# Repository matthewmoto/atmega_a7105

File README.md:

# ATMega A7105 Mesh Network Library #

# What Is This? #
The ATMega A7105 project is a radio library and mesh network stack built for the 
Arduino environment (currently only tested on ATMega328p). The radio library and
mesh library are split so you can use the radios without the mesh logic if you like.

The primary goal for this project is to allow a simple lightweight self-healing network
of microcontrollers to be able to share data easily and overcome the limitations of 
the platform (namely very little RAM and short radio range). For more details on the 
mesh topology and design, see the [Mesh Layout Section](#Mesh-Layout) below.

# Background #

In early 2015, I  bought a handful of what I thought were NRF24L01 radio breakouts
in order to make [my 2015 Halloween Decorations](https://youtu.be/kfExGzUOxbg) wireless. 
Having run 150' of security wire the previous year, accidentally cut a critical line 
partway into the set-up and collecting it all back up the next day, I had a pretty strong motivation to 
make the switch.

In my haste to buy radios, I didn't analyze the Engrish on the product page (I was buying through
DX) and ended up with a bunch of A7105 breakouts (Also known as XL7105-SY-B).

There wasn't a bunch of useful code out there for these chips (the rcgroups.com guys
were probably the most mature but they were only really using a simple protocol for 
controlling mini quadcopters).

Lamenting my poor selection and thinking to just buy the correct radios, I looked 
into the NRF24L01's further and found I didn't really dig what was available for those either (the RF24Mesh
project, cool as it is, required a master node running for all the routing to work).

As a final bad decision (I am not a smart man...), I figured I could make a general purpose lightweight mesh stack that
would solve my problems and put the 10-odd radios that I had purchased to good use.

This code is the result of those bad decisions. After having implemented the mesh, I realize
the radio hardware itself isn't that important as far as the Mesh logic goes 
(it can be adapted to the NRF24L01's or similar at some point). However, I'm using A7105's 
for now. The good news is you can get a pair of radios for under $5USD.

# Hardware #
Because the A7105 is a 3.3V chip and the Pro Mini's I use are 5V, I decided to build shields that had
logic level convertors and a voltage regulator on board so I could just plug the boards in and make them
play nicely together. Additionally, I'm using one of the GIO pins of the radio as a "WTR" pin (it basically
goes low when the radio is done transmitting or receiving so we can use an interrupt to figure out when 
data is ready to read or is done being sent over the air) and the other as the MISO line for the SPI bus. 
Unfortunately, the GIO pins on the radio aren't nice enough to go high-Z when the chip select line is high so 
I also included a tri-state buffer to do that in case this node is used on a bus with other SPI devices.
Finally, the A7105 uses a weird 2MM pitch metric header to mount so the shield also accommodates that.

If you're using 3.3V Arduino's, you won't really need any of this (except possibly the MISO tri-state buffer
if you plan on talking to other SPI devices), but I like 5V stuff since all my other hardware (relay boards, 
MOSFETS, etc) for my Halloween project are 5V.

The Eagle files for my shield are included in the code repository in the hardware/ directory and the PCB can
be ordered on [OSH Park](https://oshpark.com/shared_projects/frDcWgtm) This is not a plug, it's just 
where I had my fabricated. I included the original design files and 
Bill of Materials in case you want to make them yourself or use a different fab house. I can post the Gerber 
files if anyone wants those instead.

This is the rendering of the shield:

Here is what the assembled radio node looks like:

And here is what it looks like with the Pro Mini and XL7105 removed:

# Getting Started #

A single node mesh isn't very interesting. Thusly, to start doing things other than being a 
lonely radio singing to yourself, you'll need a pair of nodes to make a mesh.

I included a few simple example sketches to use when you're getting started with the
code. These include test programs used to develop the mesh code and actual production 
code used in the first project (my Halloween 2015 house decorations).

## Register Host Test ##
This sketch can be found at examples/register\_host\_test/atmega\_a7105.ino.  To build it, simply copy 
it to the root of the repo, and do the usual scons build/upload.

The Register Host Test example is meant to be used with the A7105 Shield, but see the hook-up instructions
in the top of the sketch if you want to rig up your own harness.  This harness is mean to be connected and 
then poked with either the Serial Mesh Interface (see below) or a sketch of your own making.

## Serial Mesh Interface ##
This is the firmware for the A7105 Serial Mesh Interface. This firmware                
runs on a Pro Mini (or other Arduino) connected to a host machine via in FTDI
serial interface.

The Serial interface runs at 115200 baud and the serial\_mon.sh script can be used
with an argument (e.g. /dev/ttyUSB0) to start communicating with the node. This is the 
most useful example and is the actual bridge firmware used for my Halloween 2015 Prop Controller
script (there is a Python library that sits on the serial port and talks to the mesh).

See the Hook-Up instructions in the comments of the sketch for help getting this connected if you aren't
using the Pro Mini shield.
                                                                                       
NOTE: All Serial commands return either the specified "Response:" response defined below or 
the universal error response that looks like this: `"ERROR,ERROR_ID,MSG\r\n"`

Where `ERROR_ID` is a non-zero integer defined below and `MSG` is a contextually helpful
plaintext ascii string to aid in identifying the issue.

All responses or interrupting data will be one or more comma delimited lines ending in `/r/n`.

Serial Commands:                                                                       
```  
  ECHO: Turns on command echoing                                                       
  Response: ECHO,<TOGGLED>
  NOTE: TOGGLED is 1/0 for on/off (respectively) (default is OFF)                      

  LISTEN: Listen for broadcast events from the mesh.
    Response: N lines of REGISTER_VALUE,REGISTER_NAME,REGISTER_VALUE\r\n
    Possible errors: A7105_Mesh_NOT_ON_MESH
    Note: No other commands may be performed during a LISTEN. To exit LISTEN,          
          pass a byte (or less than 120 bytes) and wait for the string                 
          "READY\r\n" to come back, before issuing any commands.                       
          When entering LISTEN mode, the Arduino will first send back                  
          the line "LISTEN\r\n" as an ACK that it is now listening.                    

    Possible errors: A7105_Mesh_MESH_ALREADY_JOINING
                                                                                       
  RESET:    Leave the current mesh (no longer participate), reinitialize               
            the A7105 radio and generate a new unique ID.                              
    Response: INIT,<SUCCESS>,UNIQUE_ID              
    Possible errors: A7105_Mesh_NOT_ON_MESH
    NOTE: SUCCESS is 0 or 1 for failure/success respectively and                       
          UNIQUE_ID is an ASCII_HEX string for the 2-byte unique ID                    
          generated for this instance.                                                 

  PING: Ping the mesh to get the connected nodes
    Response: PING,NODE_ID_1,NODE_ID_2,.....NODE_ID_N (where node ID's are integers of found nodes on the mesh)
    Possible errors: A7105_Mesh_NOT_ON_MESH, A7105_Mesh_BUSY

  LIST_REGISTERS: Get all register names on the mesh
    Response: LIST_REGISTERS,REGISTER_NAME_1,REGISTER_NAME_2,....,ERRORS
    Possible errors: A7105_Mesh_NOT_ON_MESH, A7105_Mesh_BUSY
    
    NOTE: The ERRORS field in the response is a numeric value (0-255)
          denoting the number of nodes that returned incomplete data
          (either the number of registers or names of registers served)
          so if this value is non-zero, the results should be considered
          incomplete

  GET_REGISTER,<REGISTER_NAME>,<FORMAT>: Get's the value of a single register identified by <REGISTER_NAME>
    Response: GET_REGISTER,REGISTER_NAME,REGISTER_VALUE
    POSSIBLE errors: A7105_Mesh_NOT_ON_MESH, A7105_Mesh_INVALID_REGISTER_INDEX
  
    NOTE: FORMAT can be "STRING" for ASCII data, "BINARY" for binary (output will be
          ASCII hex), or "UINT32" for unsigned integer data.

  SET_REGISTER,<REGISTER_NAME>,<FORMAT>,<REGISTER_VALUE>: Set's the value of a single register identified by <REGISTER_NAME>
    Response: SET_REGISTER_ACK,REGISTER_NAME
    POSSIBLE errors: A7105_Mesh_NOT_ON_MESH, A7105_Mesh_INVALID_REGISTER_INDEX, A7105_Mesh_INVALID_REGISTER_VALUE
    
    NOTE: REGISTER_VALUE is interpreted differently depending on FORMAT. If FORMAT is:
      * STRING: REGISTER_VALUE is sent as a string whose value is terminated by /r/n on
                the serial terminal (not included in value sent).
      * BINARY: REGISTER_VALUE is taken to be a byte-aligned ASCII_HEX string whose value is sent
                as a raw binary value.
      * UINT32: REGISTER_VALUE must be an ascii string representing a numerical value between
                0 and UINT32_MAX.

  VALUE_BROADCAST,<REGISTER_NAME>,<FORMAT>,<REGISTER_VALUE>: Broadcasts a value for a register (does not need to actually
                                                             be hosted).
    Response: READY 
    Possible errors: TBD
      
    NOTE: See SET_REGISTER above for possible values of FORMAT.
 
LISTEN-Mode Data (not directly associated with a command):
  REGISTER_VALUE,<REGISTER_NAME>,<REGISTER_VALUE>
  If a node pushes a REGISTER_VALUE packet out without a node-id, it is considered a value broadcast 
  and will be pushed to the serial terminal at the time of arrival, however it will not precede the 
  current operation. 
```
## Building The Code ##
The example sketches are all based on building with [arscons](https://github.com/suapapa/arscons).

However, there are a few caveats. Namely, the code expects an Arduino distribution in the resources/
directory. One is included, but needs to be unpacked first:
` cd resources/ ; unzip arduino-1.6.1-linux32.tar.xz`

Also, arscons expects the sketch name to be the same as the directory it is in (the reason while all examples
are named atmega-a7105.ino in their respective directories).

To build an example (e.g. the serial_mesh_interface example) and push it to an arduino:
```
  (from the repo root)
  $ cp examples/serial_mesh_interface/atmega_a7105.ino .
  scons ARDUINO_PORT=/dev/ttyUSB0 upload #substitute your serial port name where applicable
```

To build the current sketch (atmega_a7105.ino), type:
`scons`

To clean:
`scons -c`

To upload to your board:
`scons ARDUINO_PORT=YOUR_SERIAL_PORT upload`

Note: check out the arscons page and update your arscons.json configuration file if
you aren't running a 5V 16Mhz Pro Mini via a FTDI programmer as I am.

Also, if you are using the graphical Arduino IDE, feel free to just copy the libraries from their directories
and place in your Arduino library path. I haven't tested this method yet so it may need a little fiddling 
to get it working.

# Debugging Your Nodes #

Sometimes the mesh won't do what you want. This might be a bug, it might be your code or (most likely) it might 
be a connector that has a bit of solder on it or is bent or something else that makes me FURIOUS, AAAAAHHHHH!!!

Regardless, the best way to see what your radio is doing is to toggle the  just uncomment the line:
`#define A7105_MESH_DEBUG` in a7105_mesh.h. This will output internal state and received packet dumps to help diagnose problems.

There is also a script (one liner) in the repository called "serial_mon.sh", running it fires 
up screen and archives the output to screenlog.0
` ./serial\_mon.sh /dev/ttyUSB0`  

# Mesh Layout #

## Simplified Explanation ##
In order to ease into what is meant in this project by the word "Mesh," presented here is a 
simplified idea of how things go.

Given N nodes (nodes being ATMega microcontrollers with a radio attached), they all talk to 
each other and serve registers (values with names attached).  For a concrete example, consider
3 nodes: A, B and C.  A serves a register "Motion" that correlates to a motion sensor attached to
it. B doesn't serve any nodes, but responds to certain broadcasts (e.g. "BLOW\_FOG") and C doesn't
serve registers either, but runs a serial interface to a host computer for a program or user to poke 
the mesh.

In this example, for there to be a "Mesh," the nodes need to agree on a few things:
 1. They are on a mesh
 2. What their "node ID" is (a value from 1-255 to identify the node on the mesh).
 3. That they have a 16-bit unique ID

To do this, each node starts broadcasting (at a pseudo random interval), that it wants to join a mesh 
and that it's node ID is 1 (everybody starts at 1), and it's unique ID is whatever it is. As these packets
go out over the radio, any conflicts (duplicated node ID's ) are seen by the nodes and CONFLICT_NAME packets
are sent out as a response.  The node with the lower unique ID increments their requested node ID and starts 
the JOIN process over again. 

If a node get's through the multi-second JOIN broadcasts without having CONFLICTS come back for their selected node ID, it assumes itself 
to be "on the mesh with that ID" It's important to note, that the conflict packets can come at any time and the rules still
apply (the lower unique ID always re-joins as a different ID). It is this property that makes the mesh "self 
healing" where if two groups of nodes exist that can't talk to each other (two separate meshes) suddenly can
communicate (e.g. by moving closer together), they will conflict and re-order themselves to be a single mesh.

So, back to the example, a bunch of JOIN packets fly around. A few CONFLICT's happen and the nodes A, B and C
join as 1,2 and 3 (not necessarily in that order). Now, if node C starts sending requests to get the value of
the "Motion" register, it doesn't care what node actually hosts that value, just that one does and value 
responses come back (i.e. a nodes ID isn't considered a permanent thing).

All nodes respond to PING packets with PONG packets (for simple presence detection). The PING-ing node keeps a 
presence bitmask (255 bit) that can be used to iterate and poke every seen node on the mesh.  For discovering what
registers are available on a mesh, a node performs the following steps:
 1. PING all the nodes to find available nodes
 2. For every found node, query how many registers it serves (GET_NUM_REGISTERS packet)
 3. For the current node, iterate from 0 to N-1 (N being the number of served registers) and query the register name for each (GET_REGISTER_NAME)

If a node knows the name of the register it wants to query, it can simply send a GET_REGISTER packet with the name of the register in question
and expect a REGISTER_VALUE packet in response (assuming the node serving that register is currently available). If a node wants to remotely set a
register value, it can likewise send a SET_REGISTER packet with the name and new value of the register. For SET_REGISTER requests, a 
SET_REGISTER_ACK packet is expected to come back with either success or some error message from the remote node explaining an error (in ascii).

Beyond this, there is only one special case for getting/setting registers: value broadcasts. Since node numbering starts at 0, if a 
REGISTER_VALUE packet is seen with a node ID of 0 in the header, it is assumed to be a broadcast. These broadcasts are repeated through the
mesh by all nodes and are meant for notification of global events. They are not ACK'd by any nodes. Broadcasts can be useful if a node needs to
push a notification to the mesh rather than being polled for a value.

## Primary Canons ##
 1. As stateless as practical. Large state means high RAM usage and inflexible rules. Both are catastrophic.
 2. Requesters are responsible for retries and request state management.
 2. Global registers. Nodes serve registers, it doesn't matter who or where (at the API level).
 3. All non-broadcast packets must be ACK'd (either explicitly or with a response packet)
 4. Max of 255 nodes (0 is a special value meaning broadcast)
 5. Joining is the responsibility of good citizen nodes. There is no gatekeeper.
 6. Easy of use and reliability are the targets, security is not very important (it's a low power mesh network)
 7. Avoid traffic contention whenever possible (don't repeat packets blindly).

## Packet Characteristics ##

All packets should have the following characteristics:

```OPERATION | SEQ-NUM/HOP-COUNT | NODE_ID | UNIQUE_ID | <operation-specific-data>```

Packets are 64 bytes long at a maximum, operation specific data
is a maximum of 60 bytes long.

The packet header looks like this:
  1. Byte 0: The operation (PING, JOIN, etc)
  2. Byte 1: The sequence number and hop count (upper nibble is sequence, lower is hop)
             See notes below on these fields.
  3. Byte 2: The node-ID of the sender (1-255, 0 is reserved)  
  4. Byte 3-4: The unique-ID of the sender (1-16535, 0 is reserved)

### Hop Count ###
The hop count in the SEQ-NUM/HOP-COUNT byte is a number 0-15(max) denoting
how many times a packet has been repeated by somebody other than the sender.

When a node sends a packet normally, the hop count should be 0. Every node that
repeats the packet should do so verbatim except incrementing the hop count nibble 
by one so the next node will know whether or not the packet can be repeated again.

### Sequence Number ###
The sequence number nibble in the SEQ-NUM/HOP-COUNT byte is a number (0-15) that
is maintained by each node when sending requests (or value broadcasts). This number 
is incremented (15 + 1 rolls over to 0) after each sent packet. Thusly, two identical
requests sent back-to-back from a node can be distinguished from the same packet being
repeated by other nodes in the mesh (since we don't know the route a packet will take,
hop count cannot be used for this reliably).

## Maintaining Node Numbering ##

  To be as effective as possible at correctly assigning and maintaining
  the node numbering on the mesh as nodes come and go, each node generates
  a unique ID (16 or 32 bit, not sure yet) to be included in the packets
  they send.  This deals with the problem of joining the mesh as a certain
  node number that's already in use (the node using it will respond with a 
  CONFLICT_NAME packet) like this:
    `CONFLICT_NAME | HOP/SEQ | NODE_ID | UNIQUE_ID`

  Also, this deals with the issue of nodes that appear thinking they're
  already part of the mesh (if they were blocked or something while somebody
  joined and took their ID).

  For example, if we have 5 nodes (1-5) on the network and node 2 is blocked from 
  the mesh signals (we'll call this node ABC) for a few seconds while 
  a 6'th node (DEF) joins (taking the node 2 name).

  If a request comes from node 1 to get the listing of register names 
  from node 2 (which is actually 2 nodes thinking they're on the mesh
  right now since nobody has pinged while they're both on), they both
  will respond.

  How do we deal with ABC and DEF both thinking they're node 2? They
  can't figure it out before-hand because there isn't any traffic going
  on.  They will see each others' REGISTER_NUM response.

  The requester will process whichever REGISTER_NUM response comes first
  but the nodes themselves will likely see each other's response and 
  the one with the lower unique ID will have to re-join.

  The requester, will then likely send GET_REGISTER_NAME requests
  to the first-responding node while the other rejoins. Since there
  is only one node 2 now, everything will proceed as usual. 

  Additionally, the requester will save the unique ID of the node that
  responded to REGISTER_NUM to use for filtering GET_REGISTER_NAME 
  responses as well.

## Joining ##
  To join, a node must broadcast a "JOIN" packet at a sub-second frequency
  for multiple seconds before it can declare itself "JOINED." 
  
  The JOIN packet looks like this:
    `JOIN | HOP/SEQ | NODE_ID | UNIQUE_ID |`

  During the time it broadcasts, it must honor "CONFLICT" packets from other
  nodes. These should only come from nodes with the same NODE_ID being 
  requested but having a different UNIQUE_ID to indicate that NODE_ID is
  already taken.

  If the joining node receives a CONFLICT, it can only join by restarting
  the process with a different NODE_ID.

## Ping ##
  Detects presence prior to global operation, has timeout after which
  the Presence Table is considered accurate for the next operation.

  The PING packet looks like this:
    `PING | HOP/SEQ | NODE_ID | UNIQUE_ID`

  All nodes on the network respond (after a node-id delay) with:
    `PONG | HOP/SEQ | NODE_ID | UNIQUE_ID`

## Get Register Names (directed, retry) ##

Getting register names is available to make the mesh discoverable
with interactive terminals or more powerful hardware. The process
of getting all registers on the network is:
 1. Ping the mesh to get presence info
 2. Iterate each found node and send a GET_REGISTERS packet
 3. The node responds with the number of registers
 4. Iterate the number of registers and GET_REGISTER_NAME for each
 5. The node responds with the name of each register 

  The GET_NUM_REGISTERS packet looks like this:
    `GET_NUM_REGISTERS | HOP/SEQ | NODE_ID | UNIQUE_ID | TARGET_NODE_NUM`
  
  The NUM_REGISTERS packet response looks like this:
    `NUM_REGISTERS | HOP/SEQ | NODE_ID | UNIQUE_ID | NUM_REGISTERS`

  The GET_REGISTER_NAME packet looks like this:
    `GET_REGISTER_NAME | HOP/SEQ | NODE_ID | UNIQUE_ID | TARGET_NODE_NUM | REGISTER_INDEX`

  The response REGISTER_NAME packet looks like this:
    `REGISTER_NAME | HOP/SEQ | NODE_ID | UNIQUE_ID | REGISTER_NAME_LEN |REGISTER_NAME | REGISTER_INDEX`

  Note: If the register index is invalid, the response should just 
        have a REGISTER_NAME_LEN of 0

## Get Register ##

  The process of getting a register value is accomplished by 
  the requester sending out a broadcast packet to request
  the value of a register. The owner of that register then responds
  with a directed packet to the original requester.

  The GET_REGISTER packet looks like this:
    `GET_REGISTER | HOP/SEQ | NODE_ID | UNIQUE_ID | REGISTER_NAME_LEN | REGISTER_NAME`
   
  The responder (if there is one), sends back a REGISTER_VALUE packet like this:
    `REGISTER_VALUE | HOP/SEQ | NODE_ID | UNIQUE_ID | REGISTER_NAME_LEN | REGISTER_NAME | REGISTER_VALUE_LEN | REGISTER_VALUE`

NOTE: If NODE_ID = 0, the REGISTER_VALUE packet is considered to be a broadcast. Unique_ID must still be specified

## Set Register ##

  Setting a register is similar to getting a register value, except
  it's all in one packet so there are limits on the size of the register name/value.
  
  The SET_REGISTER packet looks like this:
    `SET_REGISTER | HOP/SEQ | NODE_ID | UNIQUE_ID |REGISTER_NAME_LEN | REGISTER_NAME | REGISTER_VALUE_LEN |REGISTER_VALUE`

  If there is a node servicing that register (and the register can be set), it responds like this:
    `SET_REGISTER_ACK | HOP/SEQ | NODE_ID | UNIQUE_ID | TARGET_NODE_NUM | ERR_MSG_DATA | NULL_BYTE`

NOTE: If there is an error setting a register and the managing node
wants it known (always a good idea), they should include an ascii 
error message at the tail (null terminated) explaining what happened
so the developer can easily diagnose issues.
If there is ERR_MSG_DATA before the NULL_BYTE, the register was set successfully.

## Node Characteristics ##

### Salt ###

  Each node has a unique ID (salt) used to handle identify conflicts.
  Nodes on a mesh are numbered 1-255, but this is handled dynamically
  so the salt is used to identify conflicts joining and for nodes
  responding to the same request if they didn't figure out the 
  conflict before it came.

### Presence Table ###

  A 255-bit bitmask (32-byte) is used to keep track of the node-id's
  seen recently for certain operations. It is refreshed only for these
  operations (like getting all registers on the mesh).

### Short Packet History ###
 
  A few (2-3 likely) packets are kept in memory to use for rebroadcasting
  packets as well as avoiding bouncing packets we already re-broadcast.
    
  This is done with a circular buffer at the moment. 

### Target Node Cache ###
  Each node saves the node-id and/or unique-id of a node it is corresponding with
  directly. These values are used to filter response packets a requesting node
  is interested in.

### Handled Request Cache ###
  This is a cache that stores metadata about recently handled requests (operation,
  sequence number, unique ID of requester) used to prevent responding to a request
  more than once as it bounces around the mesh.

### Packet Filtering ###
  Nodes filter packets for requests, responses and repeating. Below are details on the
  algorithm for each.

#### Requests ####
Requests are filtered using the "Handled Request Cache" detailed above. If a
node sees the same request it just handled, it will ignore that request.  Another
identical request from the same requesting node *will* be handled due to the fact that
the new request will almost be guaranteed to have a different sequence number than the one in the cache.    

#### Responses ####
Response packets are filtered out by utilizing the "Target Node Cache" described above.
If either a node-id and/or a unique-id are specified in the cache, only packets from those
id's will be processed by us as responses. This helps us to manage requests in the state machine such
as GET_NUM_REGISTERS where we will then know which NUM_REGISTERS packet to pay attention to
if it comes back (since it will be from the node we originally specified).

Also, this prevents us from having our target node ID swapped in the middle of long-running
operations (like retrieving the names of all registers for a given node). Once we get the 
first NUM_REGISTERS packet back, we can filter on the unique ID of the node also so we won't
get garbage from a different node if a ID swap happens.

### Packet Repeating ###
To overcome the range limitations of the tiny radios used for the Mesh, all nodes on a Mesh 
act as repeaters and repeat the packets they receive. However, this is not done blindly as
simply repeating all the packets would cause a ton of useless traffic.

Packets should be repeated up to a maximum of 16 times (tracked as "hop count"
in the packets themselves); the setting may be lower depending on the implementation. 

All packets will be repeated, *except*:
  * If the node receiving a packet is not Joined to a mesh (either joining or not connected at all).
  * The receiving node originally sent the packet (identified by node-ID and unique-ID in the packet
    header).
  * The packet was a request addressed to the receiving node directly (like GET\_NUM\_REGISTERS) or
    indirectly (like GET_REGISTER for a node that services a particular register). The idea is that
    we're the only ones that are servicing the request, so we don't need to share it further.
  * Packets we previously repeated (identical packets except with a different hop count.

See details of hop count below in the Packet Characteristics description.

### Response Repeating ###
Like the packet repeating above, nodes also maintain a cache of responses to requests they've serviced
(PING, GET_REGISTER, etc) and repeat those a few times for every response to overcome the 
inevitable packet collisions that come with multi-millisecond transmission times for packets.

Without this, there is a good chance that responses will get lost in the ether for nodes
based on random timing. Since the sender has no way to know their response made it through, we 
re-send them a few times (tunable, currently 4) at random intervals to make sure they got there.

The repeated responses have the *same* sequence number as the original packet so the general repeaters
running on other nodes can filter it out after their first repeat and not end up flooding the mesh.

As an implementors note, the repeats for things like REGISTER_VALUE can have different values than the 
original transmitted packet if it has changed from the time of the original response. This allows
the implementation to avoid caching entire packets in memory (a very sparse resource on AVR microcontrollers).

The packets that are currently repeated are:
  * PONG
  * NUM_REGISTERS
  * REGISTER_NAME
  * REGISTER_VALUE
  * SET_REGISTER_ACK

### Request Repeating ###

Each node maintains a pending request cache that saves the packet for any outgoing requests
and repeats them a few times for the same reasons we repeat responses above.

### Ignoring Duplicate Packets ###

With packet repeating functionality comes the necessity of differentiating packets a
node has handled from the delayed repeats of the same packet (so we don't handle the same
packet multiple times).

The solution implemented here is a sequence number included in the second byte of each packet.
This number (0-15) is sent with every request from a node and incremented for every subsequent
request.

Thusly, receiving nodes can differentiate between repeated packets for requests they've already
seen and the original request itself. Additionally, receiving nodes can also differentiate between
two identical (but distinct) requests sent from the same node. 

The reference implementation of this mesh has Nodes keeping a "handled packet cache" where the 
packet type, sequence number and sending node Unique-ID are kept in a rotating buffer to filter
packets that have already been acted upon.

The size of this cache is small (4 bytes for every packet) so it can be increased (and should be)
for larger meshes. A good rule of thumb is to make this cache size identical to the number of expected
nodes on the mesh -1 to handle the worst case where every node except one sends a packet at nearly 
the same time to the lone receiver. That node will then need to distinguish between the packets 
it has handled and the repeats it doesn't want).

#### Exception: The JOIN packet ####
  The one exception to the exclusion rules above are that JOIN packets are *always* repeated. 
The reasoning behind this is to maximize visibility of joining nodes to ensure we minimize node-ID
collisions.  Since JOIN packets are repeated a bunch of times while the node is joining, each 
repetition will be repeated regardless and will not be subject to the rule about repeating identical
packets.

### Auto-Rejoin and Node ID ###
The node ID of a node on a mesh can change at any time due to a CONFLICT_NAME being passed 
around. Thusly the user should not trust the ID of a node for any semblance of uniqueness.

The Node-ID is meant to be an easy way to address nodes with a limit on the number that 
can be on the mesh at any time (255) and keep the packet requirements short.

# Mesh API #

The API and main entry points are all documented in a7105\_mesh.h with explanations of parameters and 
possible return values.  Instead of duplicating it here, the reader is encouraged to study the example
programs provided and the in-code documentation.

Additionally, there are a number of packet-related magic numbers specified in a7105_mesh_packet.h that
may be helpful.

## Callback vs Blocking ##

The A7105_Mesh API is designed to have every entry point optionally have a callback
for asynchronous behavior. The novice programmer who doesn't want or need this feature
can safely pass NULL for these arguments and have the library behave as expected (i.e. the
calling code wait for the successful completion of the operation). However, the developer 
having their code perform other time-critical operations (or simply one using multiple radios
simultaneously) have the option to pass a callback to be called when the current operation
(join, get_register, ping, etc.) completes with a status code so the main event loop isn't 
monopolized by the radio code.

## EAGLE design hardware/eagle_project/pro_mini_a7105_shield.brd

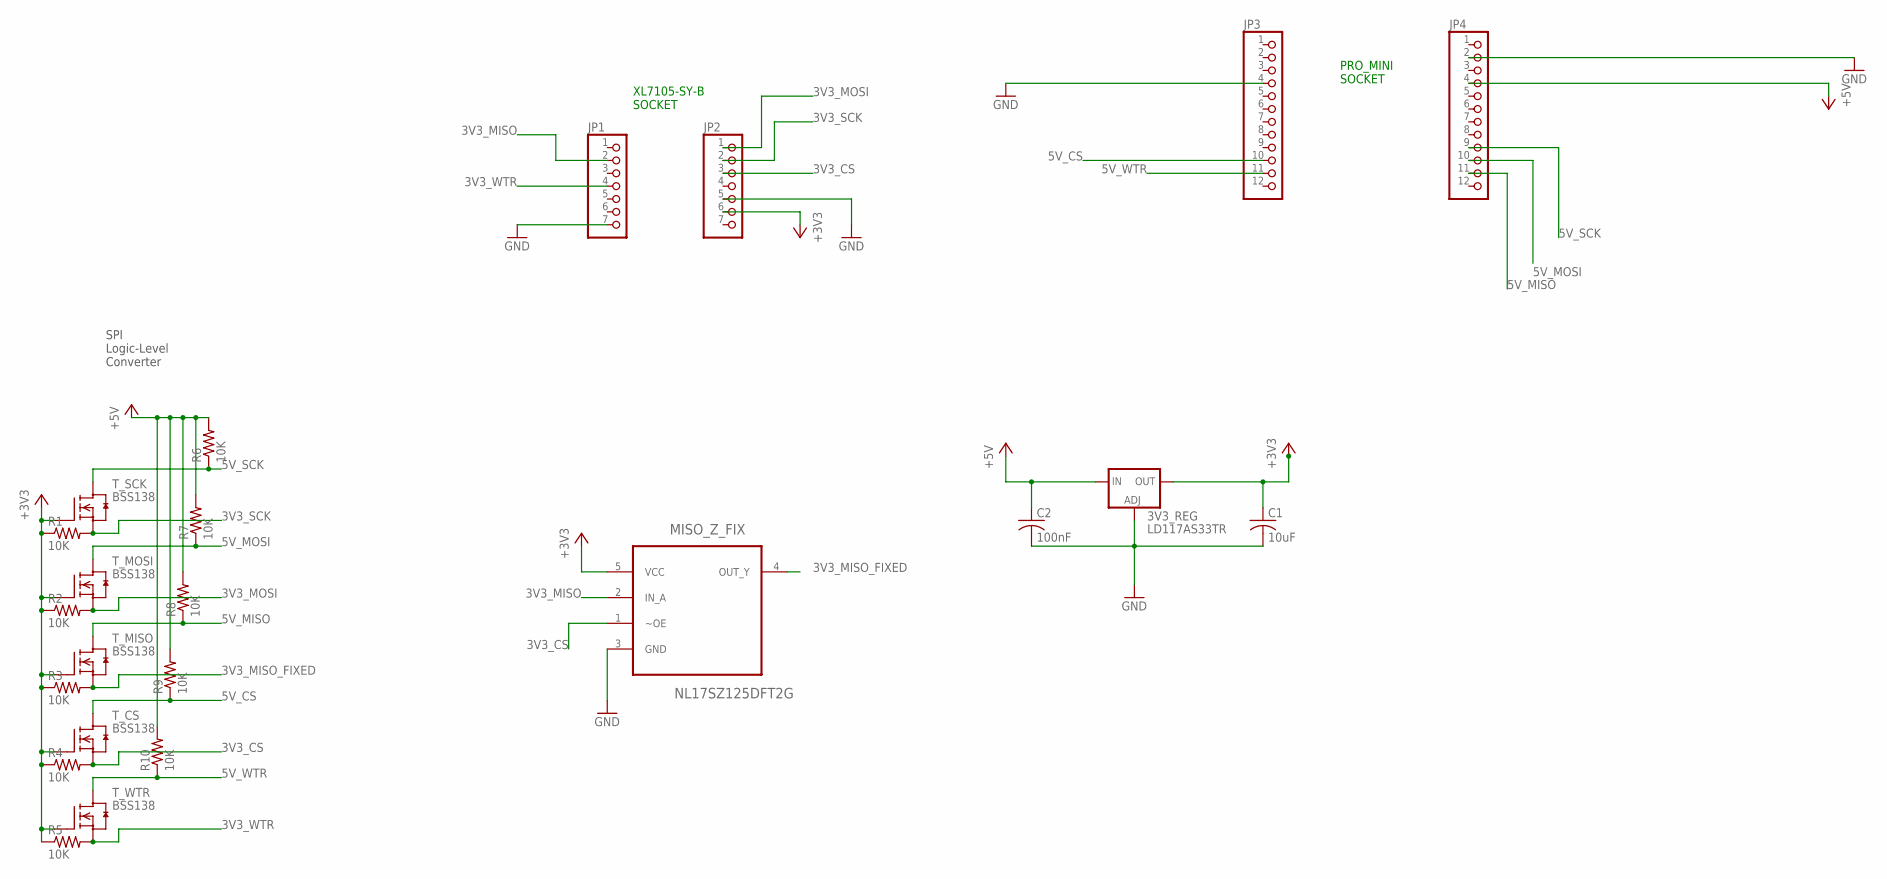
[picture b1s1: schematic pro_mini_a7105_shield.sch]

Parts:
3V3_REG: LD117AS33TR; SOT223
C1: 10uF; C0805
C2: 100nF; C0805
JP1, JP2: PINHD-1X7M; 1X07M
JP3, JP4: PINHD-1X12; 1X12
MISO_Z_FIX: NL17SZ125DFT2G; SOT65P210X110-5N
R1, R2, R3, R4, R5, R6, R7, R8, R9, R10: 10K; R0805
T_CS: BSS138; SOT23
T_MISO: BSS138; SOT23
T_MOSI: BSS138; SOT23
T_SCK: BSS138; SOT23
T_WTR: BSS138; SOT23

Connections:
3V3_CS: JP2.3, MISO_Z_FIX.1 (~OE), R4.2, T_CS.2 (S)
3V3_MISO: JP1.2, MISO_Z_FIX.2 (IN_A)
3V3_MISO_FIXED: MISO_Z_FIX.4 (OUT_Y), R3.2, T_MISO.2 (S)
3V3_MOSI: JP2.1, R2.2, T_MOSI.2 (S)
3V3_SCK: JP2.2, R1.2, T_SCK.2 (S)
3V3_WTR: JP1.4, R5.2, T_WTR.2 (S)
5V_CS: JP3.10, R9.1, T_CS.3 (D)
5V_MISO: JP4.11, R8.1, T_MISO.3 (D)
5V_MOSI: JP4.10, R7.1, T_MOSI.3 (D)
5V_SCK: JP4.9, R6.1, T_SCK.3 (D)
5V_WTR: JP3.11, R10.1, T_WTR.3 (D)
+3V3: 3V3_REG.4 (OUT), C1.1, JP2.6, MISO_Z_FIX.5 (VCC), R1.1, R2.1, R3.1, R4.1, R5.1, T_CS.1 (G), T_MISO.1 (G), T_MOSI.1 (G), T_SCK.1 (G), T_WTR.1 (G)
+5V: 3V3_REG.3 (IN), C2.1, JP4.4, R6.2, R7.2, R8.2, R9.2, R10.2
GND: 3V3_REG.1 (ADJ), C1.2, C2.2, JP1.7, JP2.5, JP3.4, JP4.2, MISO_Z_FIX.3 (GND)

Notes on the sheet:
SPI Logic-Level Converter
XL7105-SY-B SOCKET
PRO_MINI SOCKET

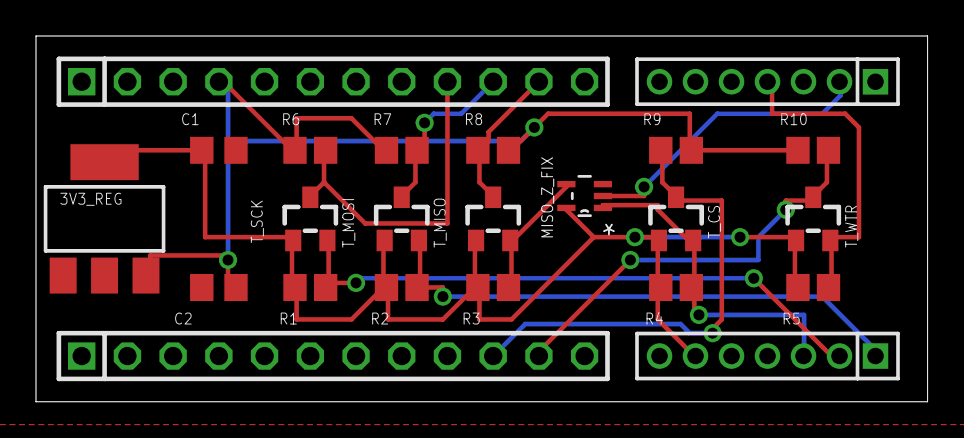
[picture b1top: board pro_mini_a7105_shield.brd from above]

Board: 2 copper layers, 49.5 x 20.3 mm, 23 parts (0 on the bottom side), 14 nets.

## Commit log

2015-03-24 Adding initial a7105 arduino code and scons build based on arduino-1.6.0 distribution.
    This code doesn't do anything except read and write a few registers.
    NOTE: The unpacked arduino distro is huge (450MB) so I just included the zipped version in git.
2015-03-25 Updates to write the base-layer a7105 library that does register read/writes and fifo access.
2015-03-26 State save of first successful run of two radios talking to each other.
    Most issues were hardware (MISO pin not being high-Z for the GPIO1 we're repurposing)
2015-03-26 More state saves for getting the a7105 library matured
2015-03-26 Adding initial check in of RX interrupt functionality working in the test harness.
2015-03-26 Updates to work on the ping back test harness. I investigated super low latency waiting for the second packet thinking there was a problem, but I seem to have must hit a timing anomaly
2015-03-26 Updating development log with progress and next steps
2015-03-27 Fixed consistency on some of the register names and added the initial round of API documentation for the a7105 library.
2015-03-27 Added CRC/FEC error stuff, updated notes and updated test harness to be way quicker and pass more data around
2015-04-01 First commit for a7105_mesh library (it works, but is incomplete and large/slow).
    Adding examples directory for all my test harnesses and new notes that track the protocol, API, TODO and development log.
    Also updating a7105 to include a function that waits for TX to complete.
2015-04-02 Updating TODO with ideas to handle unique ID collisions and updating mesh network docs about packet repeat behavior and the speical case for JOIN packets
2015-04-02 Adding GetNumRegisters() packet handling (request and response). Added Utility methods to query presence table Added cached members to track responding node id and unique id. Updated repeat filtering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
2015-04-02 Adding GetRegisterName (requset/response) and some changes to the test harness to try it out.
    Also moved all the debugging serial output to use a PGM string hack
    so it frees up some RAM (we hit the limit, now we have 550bytes free).
2015-04-02 Adding GET_REGISTER request/response handlers. Cleaning up the Register struct -> packet conversion (and vice-versa) functions a bit so we have less memcpy() stuff sitting around in the packet shuffl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
2015-04-02 Adding generic A7105_Mesh_Check_For_Timeout function instead of duplicating the same thing for every GET/SET opreration
2015-04-03 Added support for SET_REGISTER requests/responses (untested), added some Register object utility methods. Added context object support for callbacks and added callbacks for get/set registers so the v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
2015-04-03 State save after updating test harness to use regular context object and fixing some issues with SET_REGISTER
2015-04-03 Moving error string for registers to the A7105_Mesh structure. It saved over 200bytes of ram in the test harness. ~57 for each instanciated register object
2015-04-03 Fixing issues with set callbacks and adding erroneous failure message in test harness
2015-04-04 Updates to include value broadcasts and moving the Get_Error() function to the node instead of every register
2015-04-05 Upgrading "last handled packet" cache with the sequence ID methodology so we can reliably differentate between repeated packets and the original (as well as two identical original requests)
2015-04-18 Adding last commit with old laptop
2015-09-11 Adding previous updates for response-repeats, updates to development log from the last few days of active development. Also adding shield harness, probably need to clean this up
2015-09-11 Removing build litter from shield_harness project
2015-09-14 Updating test harnesses to use the higher power and higher speed radio options.
    Also updated notes (devlopment log) and fixed a few issues in the mesh lib:
    1. Now CRC/FEC error packets *aren't* propagated to the handling logic
    2. We allow repeating of packets while a node is joining to fix an issue where two meshes
    get merged when a bridging node comes online.
2015-09-14 Removing vim swp file
2015-09-15 Updates to correct requests not being repeated and correct missing debug headers for received packets
2015-09-17 Updates to work logs and bugfixes to address the following: * Packet_Clear_Error() nuking data in registers served by a node * Added A7105_Mesh_Util_RegisterNameCmp() to see if two registers refer to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
2015-09-17 Nuking untracked garbage files
2015-10-01 Updates to add speed-dependent random delays to avoid collisions (so it works more reliably across every speed range). Also commiting changes to randomize unique ID's better
2015-10-08 Adding improved random delay logic (regenerates random delay after every use to reduce periodic collision problems) also imporoved handled-request filtering using cache expiration for rolling sequenc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
2015-11-02 Removing shield-harness directory (duplication, just need the ino file present here already)
2015-11-02 Adding additional test harnesses to git
2015-11-02 Adding BSD license boilerplate and moving names from arduino_ to atmega_ so the project doesn't have the Arduino name on it
2015-11-02 More boilerplate additions and removal of old files
2015-11-02 Updating notes
2015-11-02 Removing unused a7105 reference library
2015-11-02 Removing unused cruft from references directory prior to public sharing
2015-11-02 removing unused wiring schematic prior to public sharing
2015-11-02 Adding PinChangeInt code to repo for use in building A7105 library
2015-11-02 Updating names of and removing an example (stale code)
2015-11-02 Reomving 2 radio test harness
2015-11-02 Removing stale design ideas doc (not useful anymore)
2015-11-02 Nuking development log
2015-11-02 Updating gitignore for release
2015-11-02 Removing local mirror of arscons source, it's unused and was only for reference
2015-11-02 Updating gitignore again
2015-11-02 Removing trivial make.sh script
2015-11-02 Removing unused shield harness script
2015-11-04 Updating readme for github push
2015-11-04 Fixing readme markdown
2015-11-04 Create gh-pages branch via GitHub
2015-11-04 Adding Eagle design files and hardware directory for shield
2015-11-04 Adding board images
2015-11-04 Testing markdown images for readme
2015-11-04 Updating README with more data/images
2015-11-04 Updating examples
2015-11-04 typo
2015-11-04 More formatting.....ugh markdown
2015-11-04 Spelling and wording in README.md
2015-11-04 Adding mesh notes to README
2015-11-04 Readme updates
2015-11-04 readme
2015-11-05 Removing old confusing examples in favor of easy ones
2015-11-05 state save on README.md
2015-11-05 Updating gitignore to ignore non-shared development notes
2015-11-05 Updating default sketch to be serial_mesh_interface
2023-06-19 Checking in lingering changes prior to repo-split for github upload
2023-06-19 Updating original readme to my new github account.
2023-06-19 Adding License now that the repo is public

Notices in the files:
parts and their libraries:
m-pad-2.1: License : GNU General Public License version 2 (see bottom)
